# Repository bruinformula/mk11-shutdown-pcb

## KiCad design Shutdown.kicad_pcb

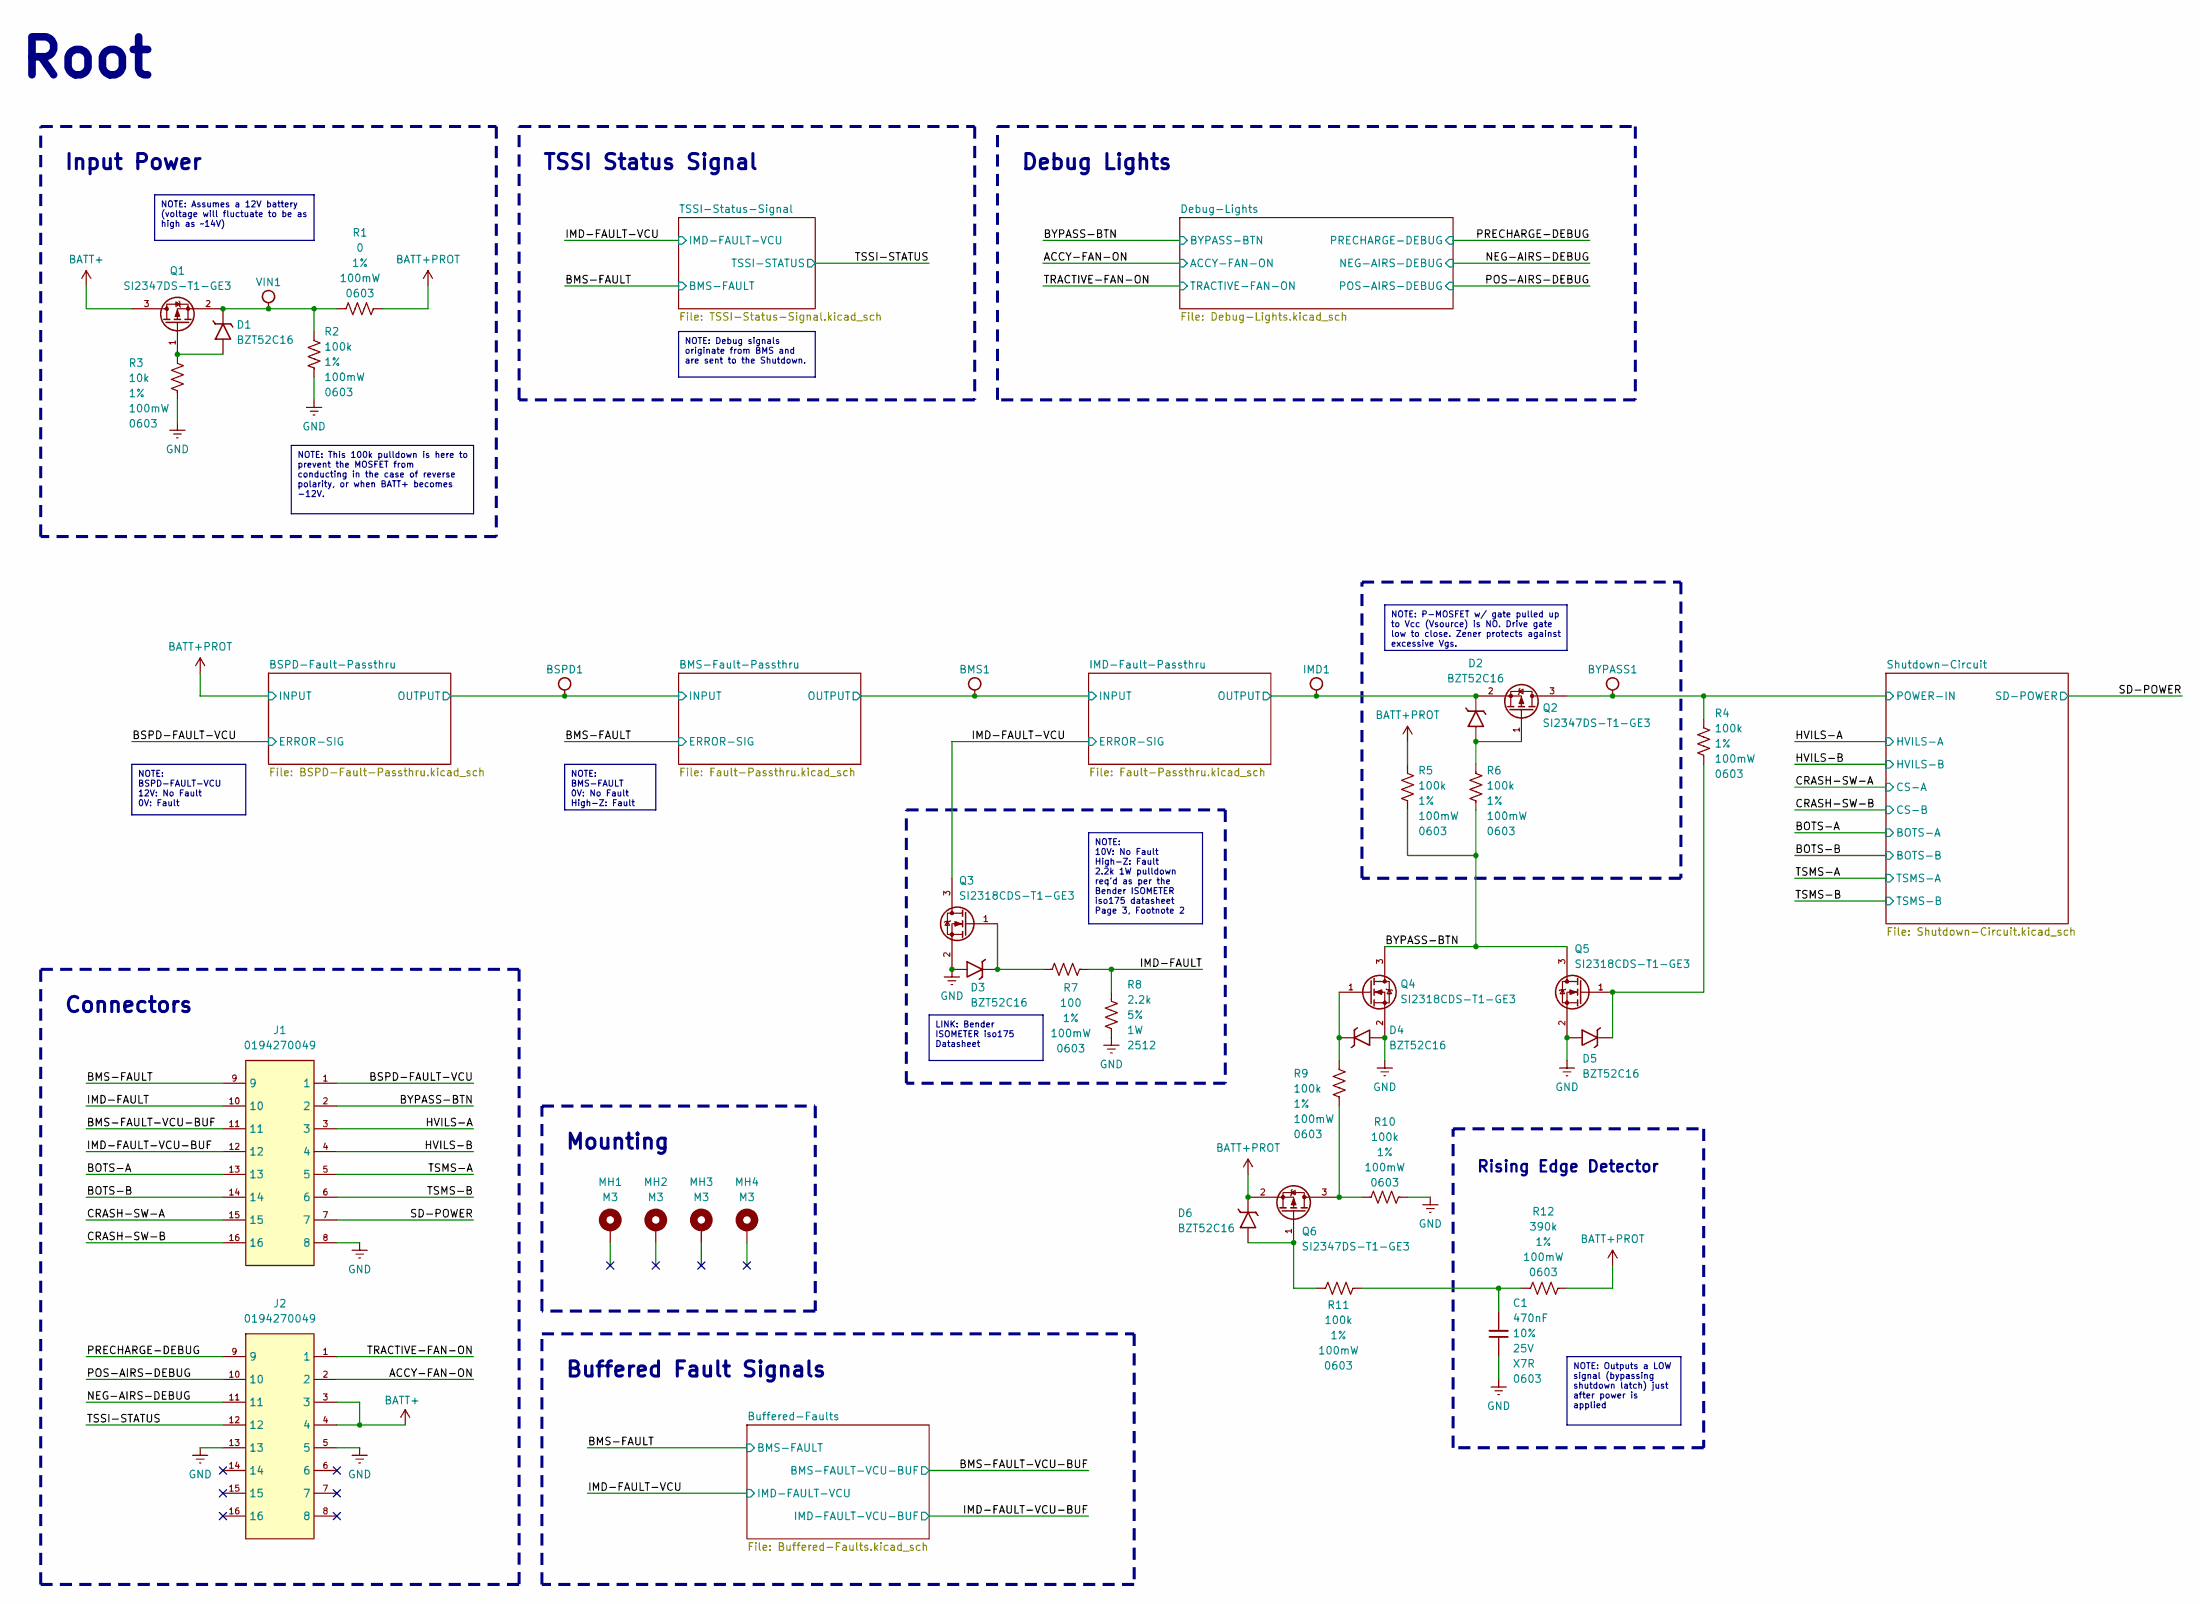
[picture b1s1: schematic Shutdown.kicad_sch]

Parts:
BMS1: TestPoint_Pad_1.0x1.0mm
BSPD1: TestPoint_Pad_1.0x1.0mm
BYPASS1: TestPoint_Pad_1.0x1.0mm
C1: 470nF; C_0603_1608Metric_Pad1.08x0.95mm_HandSolder; Tolerance 10%; Voltage 25V; Manufacturer P/N CL10B474KA8NNNC; Digikey P/N 1276-2083-1-ND
D1, D2, D3, D4, D5, D6: BZT52C16; D_SOD-123; Manufacturer P/N BZT52C16; Digikey P/N 4878-BZT52C16CT-ND
IMD1: TestPoint_Pad_1.0x1.0mm
J1, J2: 0194270049; Manufacturer P/N 0194270049; Digikey P/N WM7385-ND
MH1, MH2, MH3, MH4: MountingHole_3.5mm_Pad_TopBottom
Q1, Q2, Q6: SI2347DS-T1-GE3; SOT-23-3; Manufacturer P/N SI2347DS-T1-GE3; Digikey P/N SI2347DS-T1-GE3CT-ND
Q3, Q4, Q5: SI2318CDS-T1-GE3; SOT-23-3; Manufacturer P/N SI2318CDS-T1-GE3; Digikey P/N SI2318CDS-T1-GE3CT-ND
R1: 0; R_0603_1608Metric_Pad0.98x0.95mm_HandSolder; Tolerance 1%; Power Rating 100mW; Manufacturer P/N 0603WAF0000T5E; Digikey P/N 311-0.0GRCT-ND
R2, R4, R5, R6, R9, R10, R11: 100k; R_0603_1608Metric_Pad0.98x0.95mm_HandSolder; Tolerance 1%; Power Rating 100mW; Manufacturer P/N 0603WAF1003T5E; Digikey P/N RG16P100KBCT-ND
R3: 10k; R_0603_1608Metric_Pad0.98x0.95mm_HandSolder; Tolerance 1%; Power Rating 100mW; Manufacturer P/N 0603WAF1002T5E; Digikey P/N 541-10.0KHCT-ND
R7: 100; R_0603_1608Metric_Pad0.98x0.95mm_HandSolder; Tolerance 1%; Power Rating 100mW; Manufacturer P/N 0603WAF1000T5E; Digikey P/N 311-100HRCT-ND
R8: 2.2k; R_2512_6332Metric_Pad1.40x3.35mm_HandSolder; Tolerance 5%; Power Rating 1W; Manufacturer P/N FRC2512J222 TS; Digikey P/N RMCF2512JT2K20CT-ND
R12: 390k; R_0603_1608Metric_Pad0.98x0.95mm_HandSolder; Tolerance 1%; Power Rating 100mW; Manufacturer P/N 0603WAF3903T5E; Digikey P/N 311-390KHRCT-ND
VIN1: TestPoint_Pad_1.0x1.0mm

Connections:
/ACCY-FAN-ON: J2.2; also elsewhere on the board
/BMS-FAULT: J1.9; also elsewhere on the board
/BMS-FAULT-VCU-BUF: J1.11; also elsewhere on the board
/BMS-Fault-Passthru/INPUT: BSPD1.1 (1_1); also elsewhere on the board
/BMS-Fault-Passthru/OUTPUT: BMS1.1 (1_1); also elsewhere on the board
/BOTS-A: J1.13, J1.16; also elsewhere on the board
/BOTS-B: J1.5, J1.14; also elsewhere on the board
/BSPD-FAULT-VCU: J1.1; also elsewhere on the board
/BYPASS-BTN: J1.2, Q4.3 (D), Q5.3 (D), R5.1, R6.1; also elsewhere on the board
/CRASH-SW-A: J1.4, J1.15; also elsewhere on the board
/HVILS-A: BYPASS1.1 (1_1), J1.3, Q2.3 (D), R4.2; also elsewhere on the board
/IMD-FAULT: J1.10, R7.2, R8.2
/IMD-FAULT-VCU: Q3.3 (D); also elsewhere on the board
/IMD-FAULT-VCU-BUF: J1.12; also elsewhere on the board
/IMD-Fault-Passthru/OUTPUT: D2.1 (K), IMD1.1 (1_1), Q2.2 (S); also elsewhere on the board
/NEG-AIRS-DEBUG: J2.11; also elsewhere on the board
/POS-AIRS-DEBUG: J2.10; also elsewhere on the board
/PRECHARGE-DEBUG: J2.9; also elsewhere on the board
/SD-POWER: J1.6, J1.7; also elsewhere on the board
/TRACTIVE-FAN-ON: J2.1; also elsewhere on the board
/TSSI-STATUS: J2.12; also elsewhere on the board
BATT+: J2.3, J2.4, Q1.3 (D); also elsewhere on the board
BATT+PROT: D6.1 (K), Q6.2 (S), R1.2, R5.2, R12.2; also elsewhere on the board
GND: C1.1, D3.2 (A), D4.2 (A), D5.2 (A), J1.8, J2.5, J2.13, Q3.2 (S), Q4.2 (S), Q5.2 (S), R2.1, R3.1, R8.1, R10.2; also elsewhere on the board
unnamed: C1.2, R11.2, R12.1
unnamed: D1.2 (A), Q1.1 (G), R3.2
unnamed: D1.1 (K), Q1.2 (S), R1.1, R2.2, VIN1.1 (1_1)
unnamed: D2.2 (A), Q2.1 (G), R6.2
unnamed: D3.1 (K), Q3.1 (G), R7.1
unnamed: D4.1 (K), Q4.1 (G), R9.2
unnamed: D5.1 (K), Q5.1 (G), R4.1
unnamed: D6.2 (A), Q6.1 (G), R11.1
unnamed: Q6.3 (D), R9.1, R10.1

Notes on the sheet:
Buffered Fault Signals
Input Power
Rising Edge Detector
Debug Lights
Root
Mounting
TSSI Status Signal
Connectors
LINK: Bender ISOMETER iso175 Datasheet
NOTE: This 100k pulldown is here to prevent the MOSFET from conducting in the case of reverse polarity, or when BATT+ becomes -12V.
NOTE: Assumes a 12V battery (voltage will fluctuate to be as high as ~14V)
NOTE: Debug signals originate from BMS and are sent to the Shutdown.
NOTE: P-MOSFET w/ gate pulled up to Vcc (Vsource) is NO. Drive gate low to close. Zener protects against excessive Vgs.
NOTE: BSPD-FAULT-VCU 12V: No Fault 0V: Fault
NOTE: BMS-FAULT 0V: No Fault High-Z: Fault
NOTE: Outputs a LOW signal (bypassing shutdown latch) just after power is applied
NOTE: 10V: No Fault High-Z: Fault 2.2k 1W pulldown req'd as per the Bender ISOMETER iso175 datasheet Page 3, Footnote 2

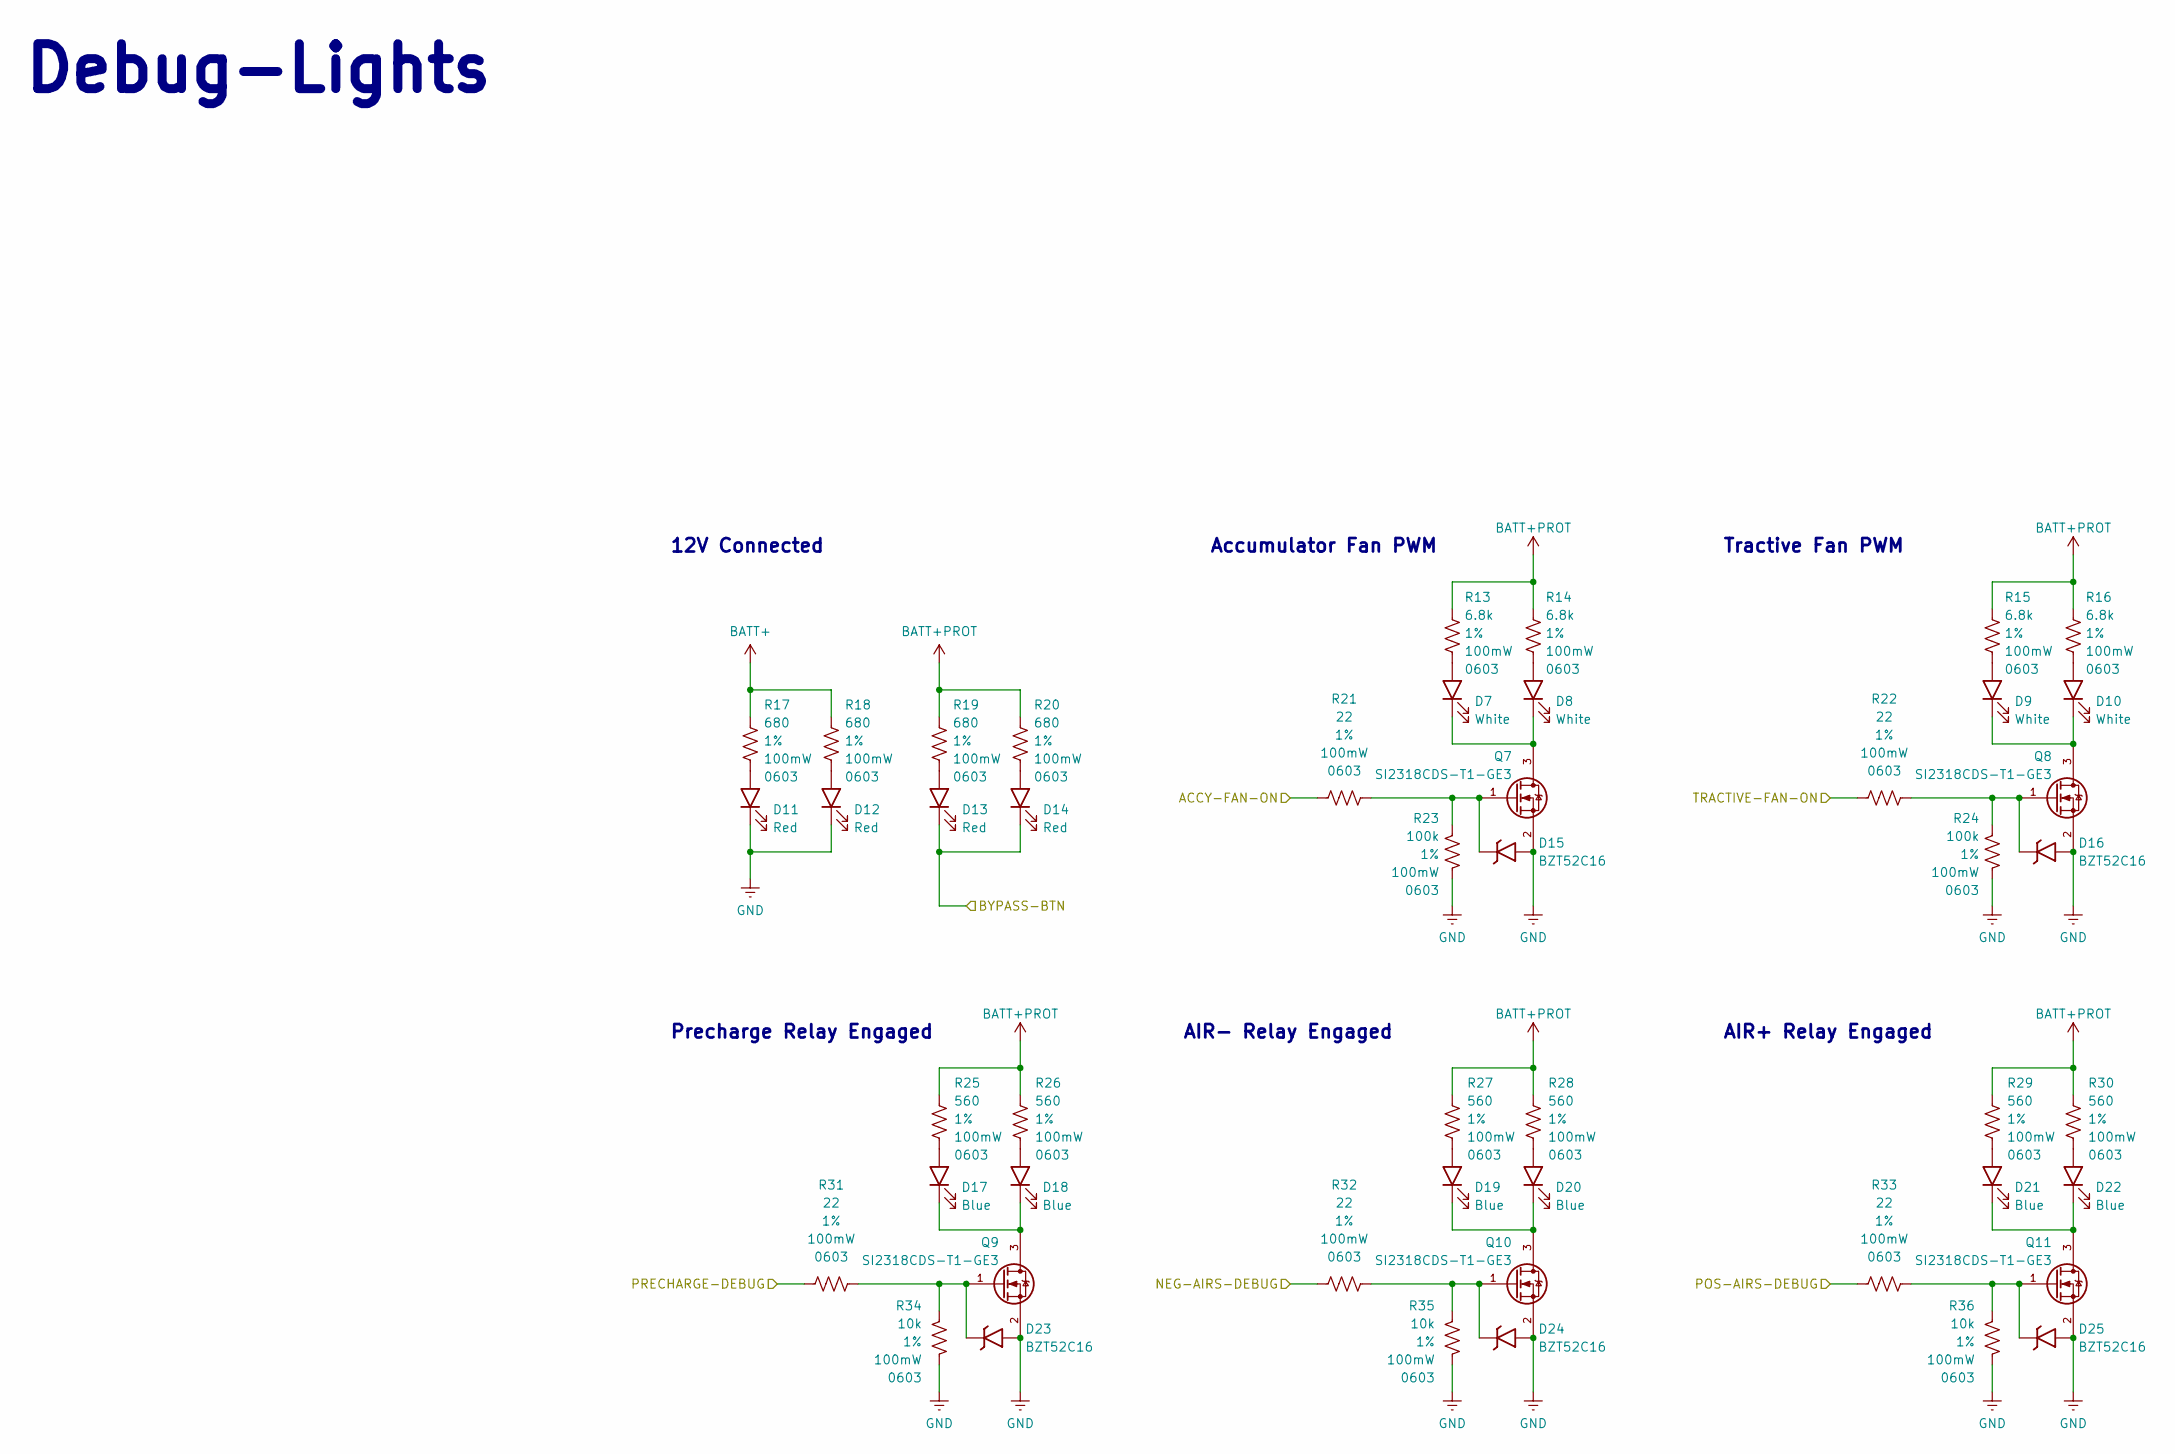
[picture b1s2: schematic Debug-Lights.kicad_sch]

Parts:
D7, D8, D9, D10: White; LED_0805_2012Metric; Manufacturer P/N KT-0805W; Digikey P/N 160-1738-1-ND
D11, D12, D13, D14: Red; LED_0805_2012Metric; Manufacturer P/N NCD0805R1; Digikey P/N 160-1427-1-ND
D15, D16, D23, D24, D25: BZT52C16; D_SOD-123; Manufacturer P/N BZT52C16; Digikey P/N 4878-BZT52C16CT-ND
D17, D18, D19, D20, D21, D22: Blue; LED_0805_2012Metric; Manufacturer P/N NCD0805B2; Digikey P/N 160-1579-1-ND
Q7, Q8, Q9, Q10, Q11: SI2318CDS-T1-GE3; SOT-23-3; Manufacturer P/N SI2318CDS-T1-GE3; Digikey P/N SI2318CDS-T1-GE3CT-ND
R13, R14, R15, R16: 6.8k; R_0603_1608Metric_Pad0.98x0.95mm_HandSolder; Tolerance 1%; Power Rating 100mW; Manufacturer P/N 0603WAF6801T5E; Digikey P/N 311-6.80KHRCT-ND
R17, R18, R19, R20: 680; R_0603_1608Metric_Pad0.98x0.95mm_HandSolder; Tolerance 1%; Power Rating 100mW; Manufacturer P/N 0603WAF6800T5E; Digikey P/N 311-680GRCT-ND
R21, R22, R31, R32, R33: 22; R_0603_1608Metric_Pad0.98x0.95mm_HandSolder; Tolerance 1%; Power Rating 100mW; Manufacturer P/N 0603WAF220JT5E; Digikey P/N 13-RC0603FR-1322RLCT-ND
R23, R24: 100k; R_0603_1608Metric_Pad0.98x0.95mm_HandSolder; Tolerance 1%; Power Rating 100mW; Manufacturer P/N 0603WAF1003T5E; Digikey P/N RG16P100KBCT-ND
R25, R26, R27, R28, R29, R30: 560; R_0603_1608Metric_Pad0.98x0.95mm_HandSolder; Tolerance 1%; Power Rating 100mW; Manufacturer P/N 0603WAF5600T5E; Digikey P/N 311-560HRCT-ND
R34, R35, R36: 10k; R_0603_1608Metric_Pad0.98x0.95mm_HandSolder; Tolerance 1%; Power Rating 100mW; Manufacturer P/N 0603WAF1002T5E; Digikey P/N 541-10.0KHCT-ND

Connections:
/ACCY-FAN-ON: R21.1; also elsewhere on the board
/BYPASS-BTN: D13.1 (K), D14.1 (K); also elsewhere on the board
/NEG-AIRS-DEBUG: R32.1; also elsewhere on the board
/POS-AIRS-DEBUG: R33.1; also elsewhere on the board
/PRECHARGE-DEBUG: R31.1; also elsewhere on the board
/TRACTIVE-FAN-ON: R22.1; also elsewhere on the board
BATT+: R17.2, R18.2; also elsewhere on the board
BATT+PROT: R13.2, R14.2, R15.2, R16.2, R19.2, R20.2, R25.2, R26.2, R27.2, R28.2, R29.2, R30.2; also elsewhere on the board
GND: D11.1 (K), D12.1 (K), D15.2 (A), D16.2 (A), D23.2 (A), D24.2 (A), D25.2 (A), Q7.2 (S), Q8.2 (S), Q9.2 (S), Q10.2 (S), Q11.2 (S), R23.1, R24.1, R34.1, R35.1, R36.1; also elsewhere on the board
unnamed: D7.2 (A), R13.1
unnamed: D7.1 (K), D8.1 (K), Q7.3 (D)
unnamed: D8.2 (A), R14.1
unnamed: D9.2 (A), R15.1
unnamed: D10.2 (A), R16.1
unnamed: D9.1 (K), D10.1 (K), Q8.3 (D)
unnamed: D11.2 (A), R17.1
unnamed: D12.2 (A), R18.1
unnamed: D13.2 (A), R19.1
unnamed: D14.2 (A), R20.1
unnamed: D15.1 (K), Q7.1 (G), R21.2, R23.2
unnamed: D16.1 (K), Q8.1 (G), R22.2, R24.2
unnamed: D17.2 (A), R25.1
unnamed: D17.1 (K), D18.1 (K), Q9.3 (D)
unnamed: D18.2 (A), R26.1
unnamed: D19.2 (A), R27.1
unnamed: D19.1 (K), D20.1 (K), Q10.3 (D)
unnamed: D20.2 (A), R28.1
unnamed: D21.2 (A), R29.1
unnamed: D21.1 (K), D22.1 (K), Q11.3 (D)
unnamed: D22.2 (A), R30.1
unnamed: D23.1 (K), Q9.1 (G), R31.2, R34.2
unnamed: D24.1 (K), Q10.1 (G), R32.2, R35.2
unnamed: D25.1 (K), Q11.1 (G), R33.2, R36.2

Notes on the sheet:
Debug-Lights
AIR+ Relay Engaged
Accumulator Fan PWM
Tractive Fan PWM
12V Connected
AIR- Relay Engaged
Precharge Relay Engaged

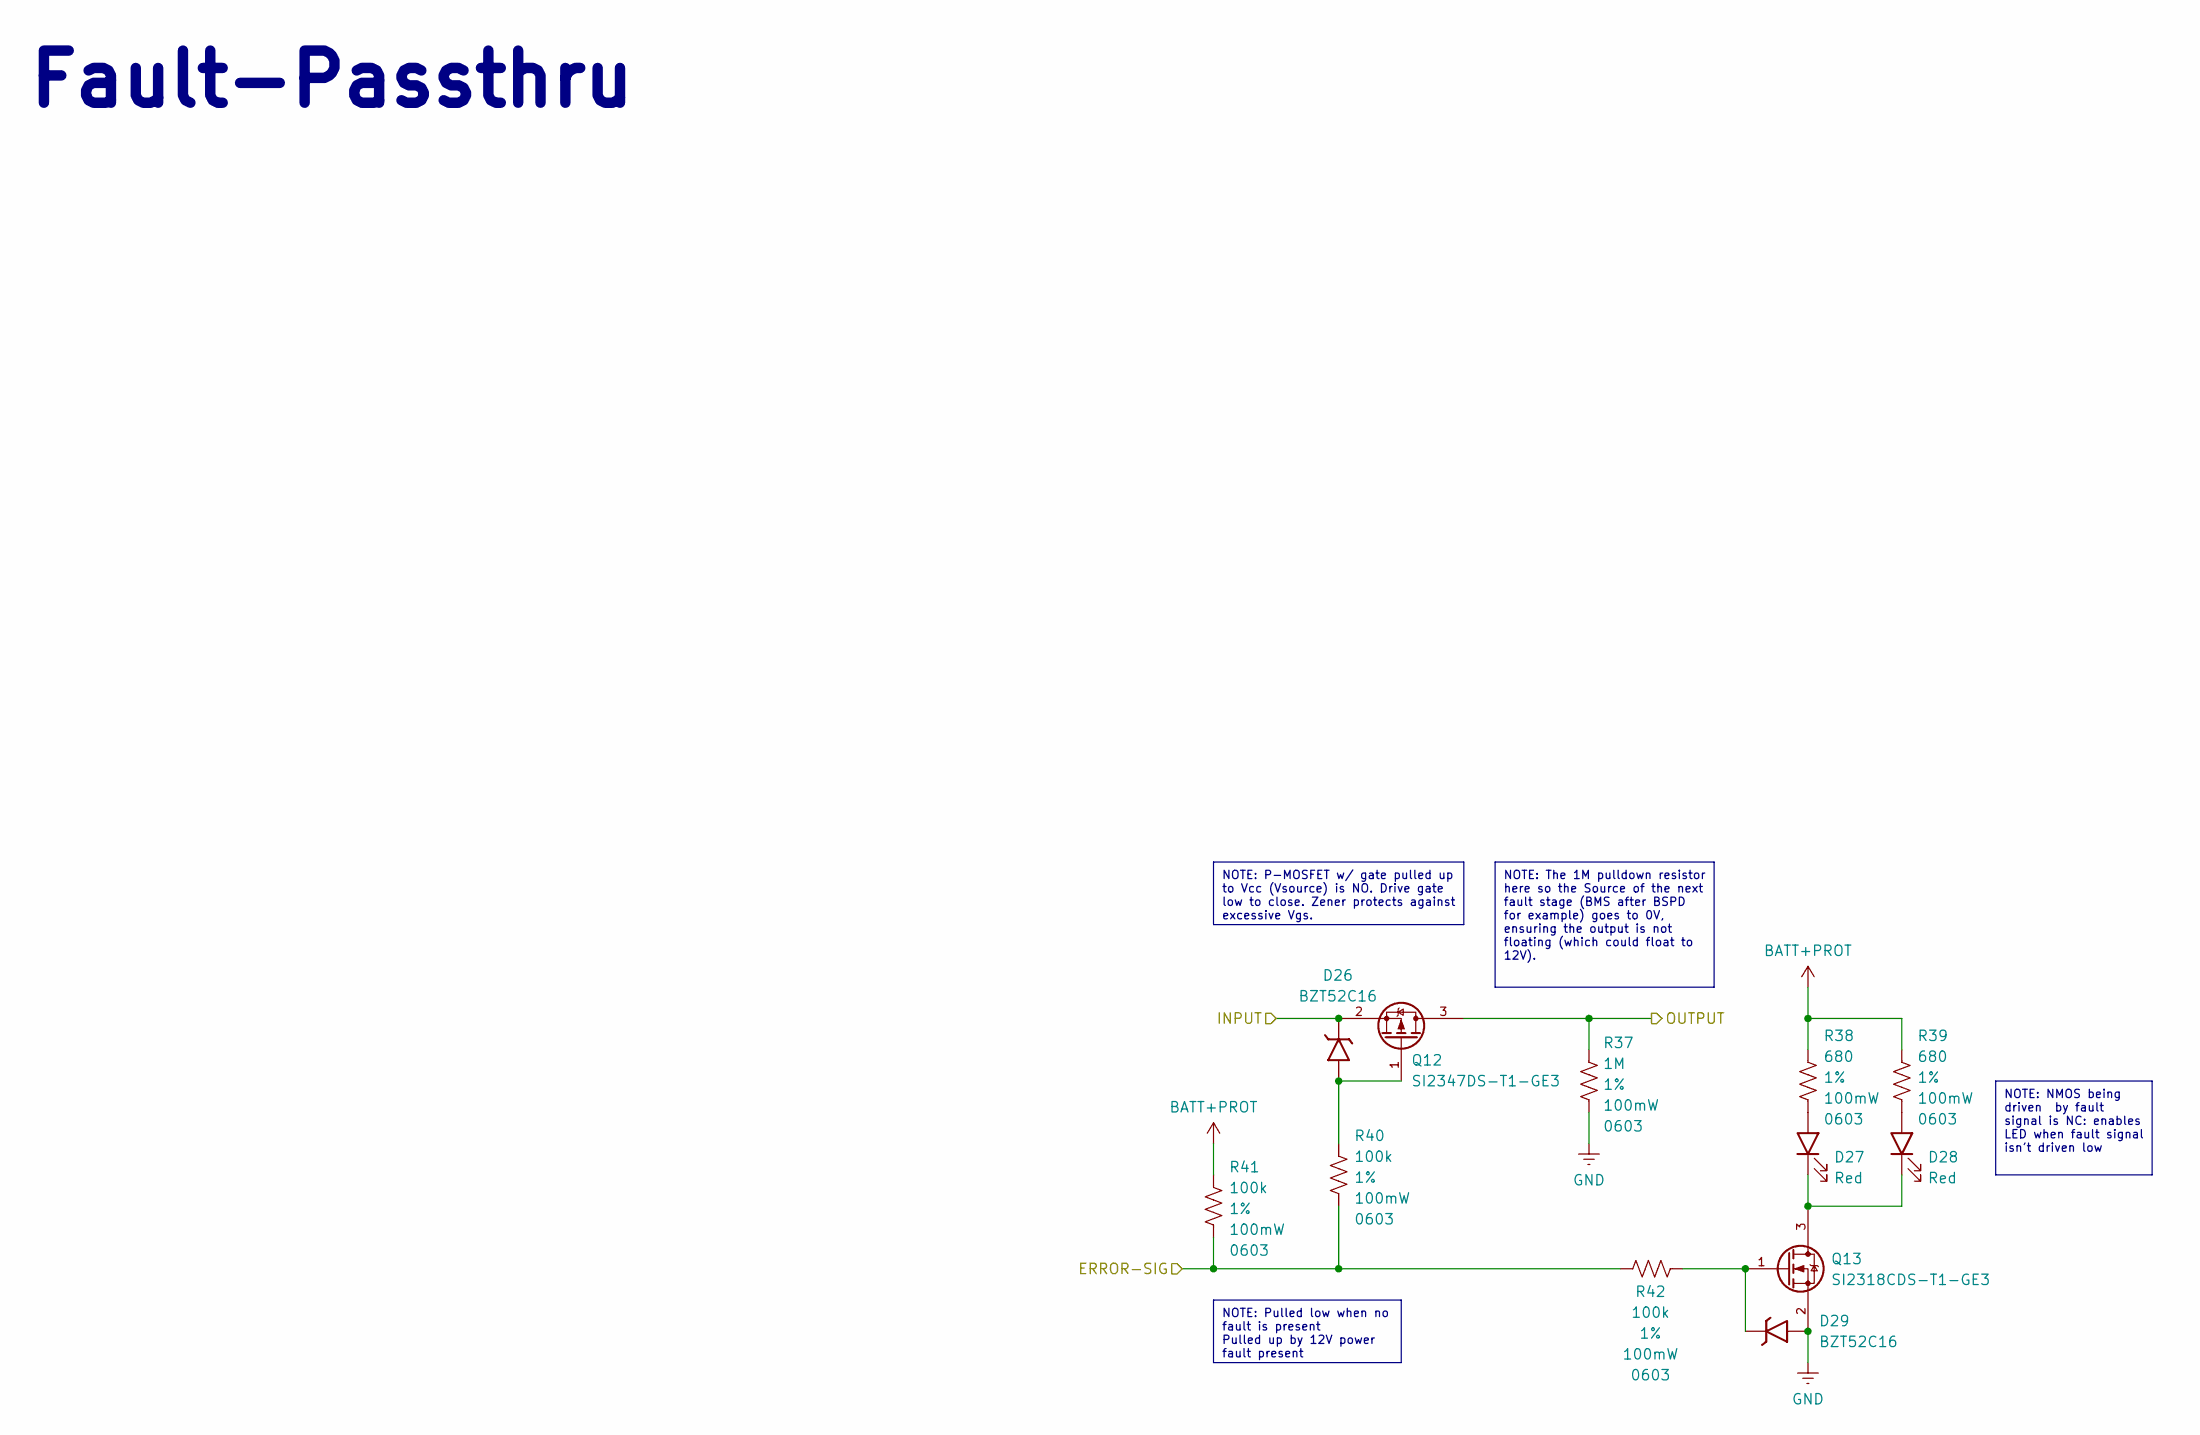
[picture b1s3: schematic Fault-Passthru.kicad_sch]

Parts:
D26, D29: BZT52C16; D_SOD-123; Manufacturer P/N BZT52C16; Digikey P/N 4878-BZT52C16CT-ND
D27, D28: Red; LED_0805_2012Metric; Manufacturer P/N NCD0805R1; Digikey P/N 160-1427-1-ND
Q12: SI2347DS-T1-GE3; SOT-23-3; Manufacturer P/N SI2347DS-T1-GE3; Digikey P/N SI2347DS-T1-GE3CT-ND
Q13: SI2318CDS-T1-GE3; SOT-23-3; Manufacturer P/N SI2318CDS-T1-GE3; Digikey P/N SI2318CDS-T1-GE3CT-ND
R37: 1M; R_0603_1608Metric_Pad0.98x0.95mm_HandSolder; Tolerance 1%; Power Rating 100mW; Manufacturer P/N 0603WAF1004T5E; Digikey P/N YAG4498CT-ND
R38, R39: 680; R_0603_1608Metric_Pad0.98x0.95mm_HandSolder; Tolerance 1%; Power Rating 100mW; Manufacturer P/N 0603WAF6800T5E; Digikey P/N 311-680GRCT-ND
R40, R41, R42: 100k; R_0603_1608Metric_Pad0.98x0.95mm_HandSolder; Tolerance 1%; Power Rating 100mW; Manufacturer P/N 0603WAF1003T5E; Digikey P/N RG16P100KBCT-ND

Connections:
/BMS-FAULT: R40.1, R41.1, R42.1; also elsewhere on the board
/BMS-Fault-Passthru/INPUT: D26.1 (K), Q12.2 (S); also elsewhere on the board
/BMS-Fault-Passthru/OUTPUT: Q12.3 (D), R37.2; also elsewhere on the board
BATT+PROT: R38.2, R39.2, R41.2; also elsewhere on the board
GND: D29.2 (A), Q13.2 (S), R37.1; also elsewhere on the board
unnamed: D26.2 (A), Q12.1 (G), R40.2
unnamed: D27.2 (A), R38.1
unnamed: D27.1 (K), D28.1 (K), Q13.3 (D)
unnamed: D28.2 (A), R39.1
unnamed: D29.1 (K), Q13.1 (G), R42.2

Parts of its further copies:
D30, D33: BZT52C16; D_SOD-123; Manufacturer P/N BZT52C16; Digikey P/N 4878-BZT52C16CT-ND
D31, D32: Red; LED_0805_2012Metric; Manufacturer P/N NCD0805R1; Digikey P/N 160-1427-1-ND
Q14: SI2347DS-T1-GE3; SOT-23-3; Manufacturer P/N SI2347DS-T1-GE3; Digikey P/N SI2347DS-T1-GE3CT-ND
Q15: SI2318CDS-T1-GE3; SOT-23-3; Manufacturer P/N SI2318CDS-T1-GE3; Digikey P/N SI2318CDS-T1-GE3CT-ND
R43: 1M; R_0603_1608Metric_Pad0.98x0.95mm_HandSolder; Tolerance 1%; Power Rating 100mW; Manufacturer P/N 0603WAF1004T5E; Digikey P/N YAG4498CT-ND
R44, R45: 680; R_0603_1608Metric_Pad0.98x0.95mm_HandSolder; Tolerance 1%; Power Rating 100mW; Manufacturer P/N 0603WAF6800T5E; Digikey P/N 311-680GRCT-ND
R46, R47, R48: 100k; R_0603_1608Metric_Pad0.98x0.95mm_HandSolder; Tolerance 1%; Power Rating 100mW; Manufacturer P/N 0603WAF1003T5E; Digikey P/N RG16P100KBCT-ND

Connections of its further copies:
/BMS-Fault-Passthru/OUTPUT: D30.1 (K), Q14.2 (S); also elsewhere on the board
/IMD-FAULT-VCU: R46.1, R47.1, R48.1; also elsewhere on the board
/IMD-Fault-Passthru/OUTPUT: Q14.3 (D), R43.2; also elsewhere on the board
BATT+PROT: R44.2, R45.2, R47.2; also elsewhere on the board
GND: D33.2 (A), Q15.2 (S), R43.1; also elsewhere on the board
unnamed: D30.2 (A), Q14.1 (G), R46.2
unnamed: D31.2 (A), R44.1
unnamed: D31.1 (K), D32.1 (K), Q15.3 (D)
unnamed: D32.2 (A), R45.1
unnamed: D33.1 (K), Q15.1 (G), R48.2

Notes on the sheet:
Fault-Passthru
NOTE: Pulled low when no fault is present Pulled up by 12V power fault present
NOTE: The 1M pulldown resistor here so the Source of the next fault stage (BMS after BSPD for example) goes to 0V, ensuring the output is not floating (which could float to 12V).
NOTE: NMOS being driven by fault signal is NC: enables LED when fault signal isn't driven low
NOTE: P-MOSFET w/ gate pulled up to Vcc (Vsource) is NO. Drive gate low to close. Zener protects against excessive Vgs.

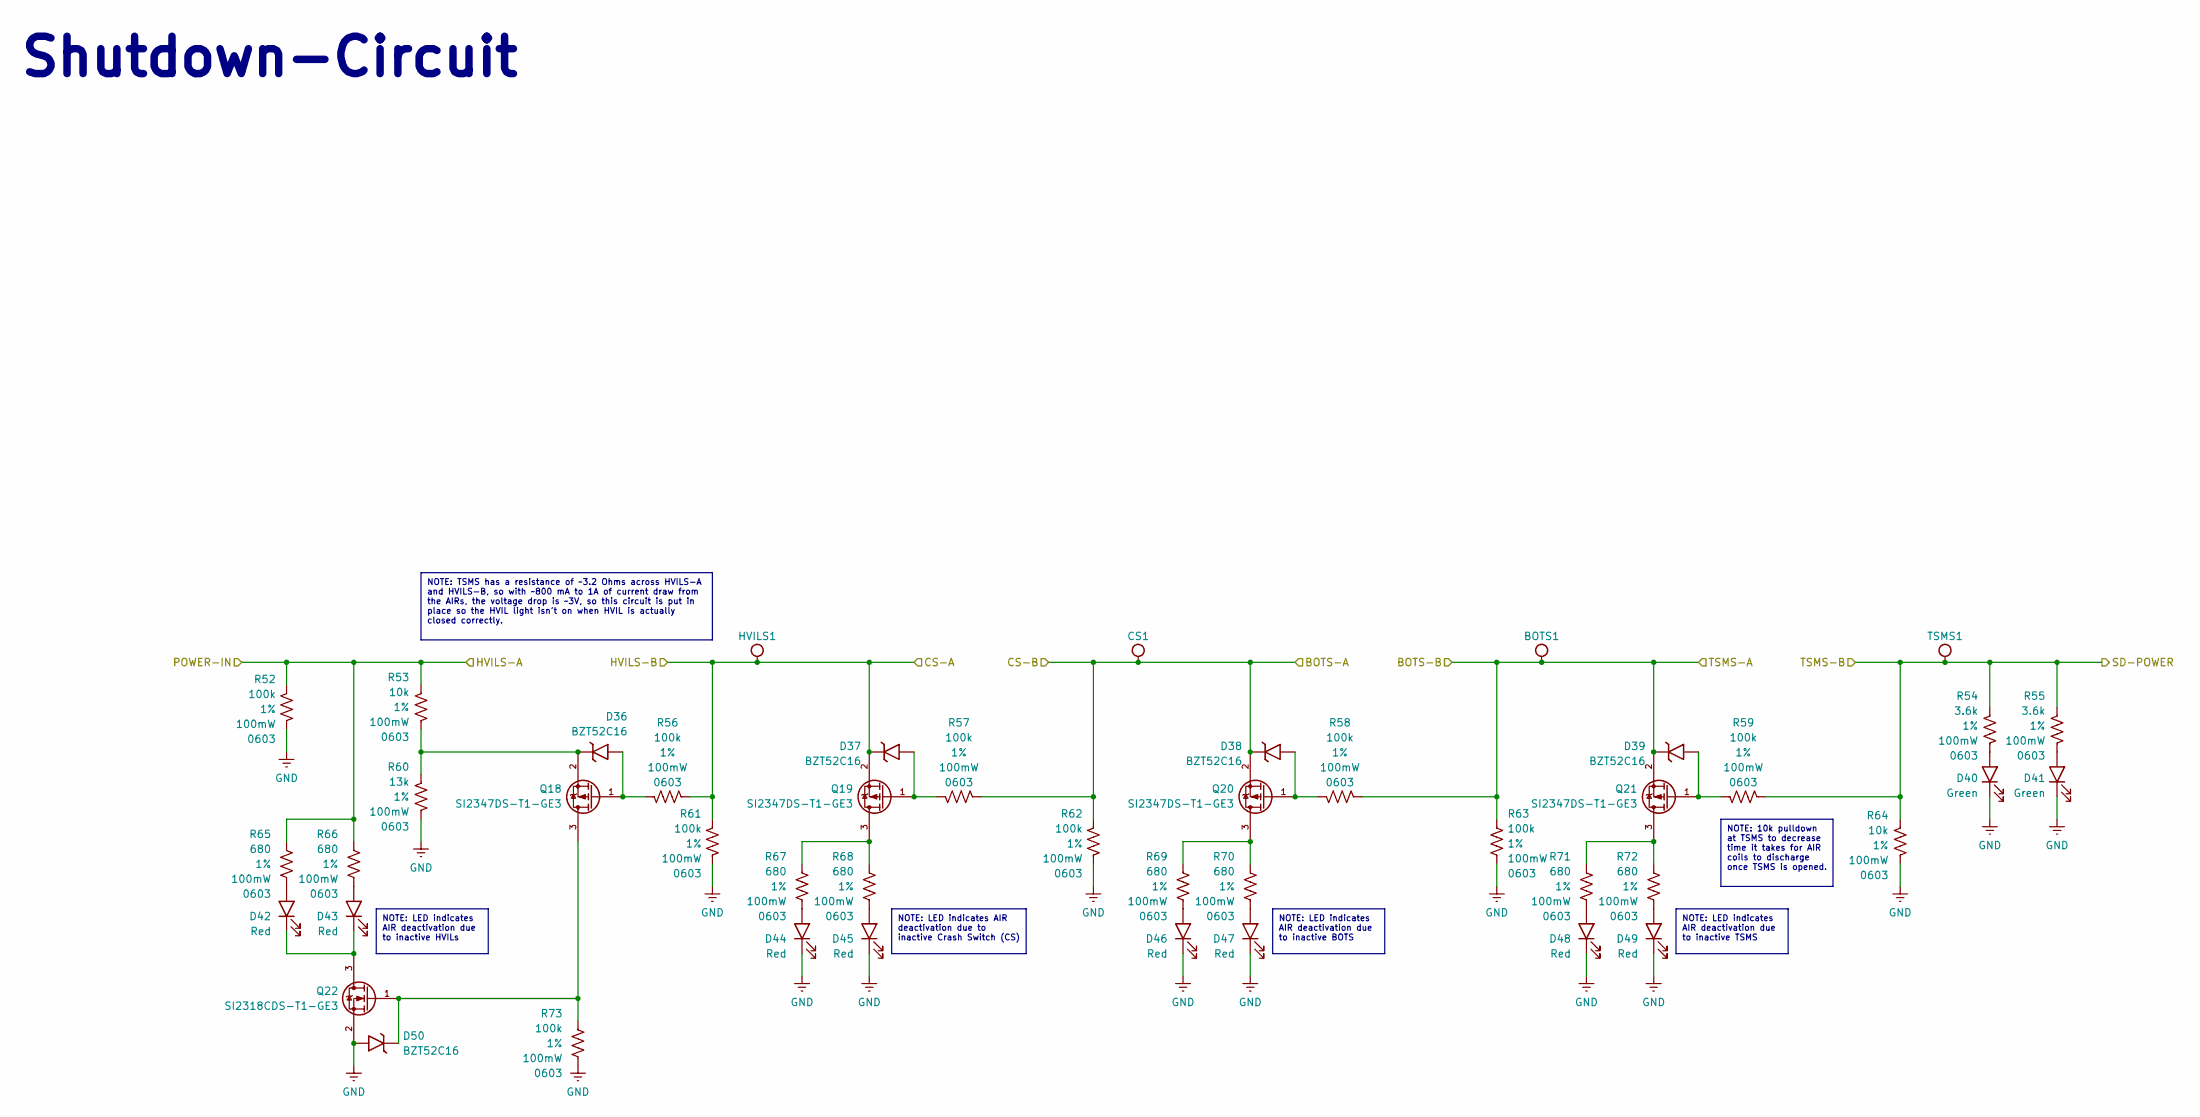
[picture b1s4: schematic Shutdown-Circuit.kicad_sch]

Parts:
BOTS1: BOTS; TestPoint_Pad_1.0x1.0mm
CS1: CS; TestPoint_Pad_1.0x1.0mm
D36, D37, D38, D39, D50: BZT52C16; D_SOD-123; Manufacturer P/N BZT52C16; Digikey P/N 4878-BZT52C16CT-ND
D40, D41: Green; LED_0805_2012Metric; Manufacturer P/N NCD0805G1; Digikey P/N 160-1426-1-ND
D42, D43, D44, D45, D46, D47, D48, D49: Red; LED_0805_2012Metric; Manufacturer P/N NCD0805R1; Digikey P/N 160-1427-1-ND
HVILS1: HVILS; TestPoint_Pad_1.0x1.0mm
Q18, Q19, Q20, Q21: SI2347DS-T1-GE3; SOT-23-3; Manufacturer P/N SI2347DS-T1-GE3; Digikey P/N SI2347DS-T1-GE3CT-ND
Q22: SI2318CDS-T1-GE3; SOT-23-3; Manufacturer P/N SI2318CDS-T1-GE3; Digikey P/N SI2318CDS-T1-GE3CT-ND
R52, R56, R57, R58, R59, R61, R62, R63, R73: 100k; R_0603_1608Metric_Pad0.98x0.95mm_HandSolder; Tolerance 1%; Power Rating 100mW; Manufacturer P/N 0603WAF1003T5E; Digikey P/N RG16P100KBCT-ND
R53, R64: 10k; R_0603_1608Metric_Pad0.98x0.95mm_HandSolder; Tolerance 1%; Power Rating 100mW; Manufacturer P/N 0603WAF1002T5E; Digikey P/N 541-10.0KHCT-ND
R54, R55: 3.6k; R_0603_1608Metric_Pad0.98x0.95mm_HandSolder; Tolerance 1%; Power Rating 100mW; Manufacturer P/N 0603WAF3601T5E; Digikey P/N 311-3.60KHRCT-ND
R60: 13k; R_0603_1608Metric_Pad0.98x0.95mm_HandSolder; Tolerance 1%; Power Rating 100mW; Manufacturer P/N 0603WAF1302T5E; Digikey P/N RMCF0603FT13K0CT-ND
R65, R66, R67, R68, R69, R70, R71, R72: 680; R_0603_1608Metric_Pad0.98x0.95mm_HandSolder; Tolerance 1%; Power Rating 100mW; Manufacturer P/N 0603WAF6800T5E; Digikey P/N 311-680GRCT-ND
TSMS1: TSMS; TestPoint_Pad_1.0x1.0mm

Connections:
/BOTS-A: CS1.1 (1_1), D38.1 (K), Q20.2 (S), R57.1, R62.2; also elsewhere on the board
/BOTS-B: BOTS1.1 (1_1), D39.1 (K), Q21.2 (S), R58.1, R63.2; also elsewhere on the board
/CRASH-SW-A: D37.1 (K), HVILS1.1 (1_1), Q19.2 (S), R56.1, R61.2; also elsewhere on the board
/HVILS-A: R52.2, R53.2, R65.2, R66.2; also elsewhere on the board
/SD-POWER: R54.2, R55.2, R59.1, R64.2, TSMS1.1 (1_1); also elsewhere on the board
GND: D40.1 (K), D41.1 (K), D44.1 (K), D45.1 (K), D46.1 (K), D47.1 (K), D48.1 (K), D49.1 (K), D50.2 (A), Q22.2 (S), R52.1, R60.1, R61.1, R62.1, R63.1, R64.1, R73.1; also elsewhere on the board
unnamed: D36.2 (A), Q18.1 (G), R56.2
unnamed: D36.1 (K), Q18.2 (S), R53.1, R60.2
unnamed: D37.2 (A), Q19.1 (G), R57.2
unnamed: D38.2 (A), Q20.1 (G), R58.2
unnamed: D39.2 (A), Q21.1 (G), R59.2
unnamed: D40.2 (A), R54.1
unnamed: D41.2 (A), R55.1
unnamed: D42.2 (A), R65.1
unnamed: D42.1 (K), D43.1 (K), Q22.3 (D)
unnamed: D43.2 (A), R66.1
unnamed: D44.2 (A), R67.1
unnamed: D45.2 (A), R68.1
unnamed: D46.2 (A), R69.1
unnamed: D47.2 (A), R70.1
unnamed: D48.2 (A), R71.1
unnamed: D49.2 (A), R72.1
unnamed: D50.1 (K), Q18.3 (D), Q22.1 (G), R73.2
unnamed: Q19.3 (D), R67.2, R68.2
unnamed: Q20.3 (D), R69.2, R70.2
unnamed: Q21.3 (D), R71.2, R72.2

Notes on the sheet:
Shutdown-Circuit
NOTE: 10k pulldown at TSMS to decrease time it takes for AIR coils to discharge once TSMS is opened.
NOTE: LED indicates AIR deactivation due to inactive HVILs
NOTE: LED indicates AIR deactivation due to inactive BOTS
NOTE: LED indicates AIR deactivation due to inactive Crash Switch (CS)
NOTE: LED indicates AIR deactivation due to inactive TSMS
NOTE: TSMS has a resistance of ~3.2 Ohms across HVILS-A and HVILS-B, so with ~800 mA to 1A of current draw from the AIRs, the voltage drop is ~3V, so this circuit is put in place so the HVIL light isn't on when HVIL is actually closed correctly.
